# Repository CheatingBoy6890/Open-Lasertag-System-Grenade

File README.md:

<div align="center">

###### Partnering with PCBway.
</div>
<br/>

# Open-Lasertag-System

##  ⚠️Warning⚠️ while this code works it is still wip and could have some bugs
---

https://commons.wikimedia.org/w/index.php?curid=1668938

Warning: This project uses lasers. Be sure to **always** do your own testing by meassuring voltage and current and by looking in datasheets. I am **not** responsible for any injuries you encounter from using this project. Also make sure to wear proper eye-protection.

---

<h2>What is Open-Lasertag-System?</h2>
Open-Lasertag-System is our approach to a build Lasertag that can be played anywhere without the need of setting up repeaters or servers, whilst beeing pretty easy to build and extend to fit your needs. It works decentral using a WIFI mesh,so the range and fun extends the more players you have!

Currently the project consists of five parts:

1.  The Taggers are fully functional with features such as different firemodes and score synchronization
2.  The vests are functional and connect wirelessly with the corresponding tagger
3.  Targets : For those who don't want to shoot at each other can just shoot at these. The plan also ist to intergrate the further into the system for modes like capture the Flag
4.  Logger: Counts wich target have been hit by whom
5.  There's a Laser grenade WIP

---

<h2>What is this repository?</h2>

This is the repository for the grenades of the system. here you'll find all the neccessary files on how to build a grenade your self.

**The instructions on building can be found in the <a href="https://github.com/CheatingBoy6890/Open-Lasertag-System-Grenade/tree/main/Hardware">Hardware folder</a>**

**What you'll need:**

- A 3D-printer capable of printing 20cmx20cm
- Soldering iron
- An ESP 8266 wemos d1 mini
- A piece of LED strip 8 LEDs ws2812b
- At least slightly transparent filament
-  perf matrix board or PCB (comming soon)
- Cable
- Pin headers
- Crimp equipment and or breadboard cables
- Tsop 4838
- 1 IR LED
- 10kΩ resistor
- bc 637 transistor
- 1x Button
- Switch
- Resistor 25Ω
- Battery holder 3 AA batteries
- 4x 6mmx30mm metal rod or pipe

- Time

  ## Who are we?

  We are two German students. Since we are twins, we build and programm a lot of projects together. We create all of our projects in our free time. Feel free to mail any questions to cyberfox3801@proton.me .
  We want to motivate people to discover what is possible using 3D printing and microcontrollers. \
  The most productive worker of our small group is our cat Susi. 

Congratulations you made it to the end of this readme. If you want this to be longer consider buying us a coffe (https://www.paypal.com/donate/?hosted_button_id=2RZBTA5GMNH6S) so we can make all files longer and better
and don't forget to cuddle your cat!

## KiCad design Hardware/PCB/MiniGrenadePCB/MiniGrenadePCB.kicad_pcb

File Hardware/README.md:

<div align="center">

###### Partnering with PCBway.
</div>
<br/>

# Hardware
## General Information 

Warning: This project uses lasers. Be sure to **always** do your own testing by meassuring voltage and current and by looking in datasheets. I am **not** responsible for any injuries you encounter from using this project. Also make sure to wear proper eye-protection.

## Where to get the components
The components are mostly standard components. We recommend buying them in a local store if possible to support the remaining stores.

We recommend ordering the PCBs at PCBWay, because they offer fast delivery and good quality at a low cost.
If you don't have a 3D printer you can also order the parts at PCBWay.

-----

**The Grenade runs using 3 1,2V NiMh batteries! Don't use voltages greater than 5V in order to power it.**

----

  **We recommend not to use a laser diode for the grenade, since it can be dangerous. Use a normal IR LED instead.** 

## The code

To flash the program to your ESP8266 you need to have <a href="https://code.visualstudio.com/">Visual Studio Code</a> and the platformio extension installed. If you haven't you can follow this tutorial:
<a>https://randomnerdtutorials.com/vs-code-platformio-ide-esp32-esp8266-arduino/</a> To flash an ESP8266 from Windows you might need additional drivers, you'll find a tutorial on this here https://randomnerdtutorials.com/install-esp32-esp8266-usb-drivers-cp210x-windows/

## Building the Grenade

#### Perf matrix board
If you're using a perf matrix board, make sure to cut out a 6x6 cm square.

#### PCB
We created the pcb layout with <a href="https://www.kicad.org/">KiCad</a>. You can easily order really nice high-quality PCBs from our partner [PCBWay](www.pcbway.com) by using the PCBWay plugin in KiCAD following this [turorial](https://www.pcbway.com/blog/News/PCBWay_Plug_In_for_KiCad_3ea6219c.html), exporting the gerber files manually like explained [here](https://www.pcbway.com/blog/help_center/How_to_Generate_Gerber_and_Drill_Files_in_KiCad_7_0_ab0d12bb.html) or use the gerber files in the repository (possibly outdated or not-yet available).

----

1. Make sure you have got all the required parts
2. Solder pins to your ESP d1 mini   - Make sure that the ESP8266 board is facing the top. (check and cross from pixabay Bild von <a href="https://pixabay.com/de/users/janjf93-3084263/?utm_source=link-attribution&utm_medium=referral&utm_campaign=image&utm_content=2061132">Jan</a> auf <a href="https://pixabay.com/de//?utm_source=link-attribution&utm_medium=referral&utm_campaign=image&utm_content=2061132">Pixabay</a> Bild von <a href="https://pixabay.com/de/users/openclipart-vectors-30363/?utm_source=link-attribution&utm_medium=referral&utm_campaign=image&utm_content=1292787">OpenClipart-Vectors</a> auf <a href="https://pixabay.com/de//?utm_source=link-attribution&utm_medium=referral&utm_campaign=image&utm_content=1292787">Pixabay</a>
3. Flash the ESP
5. Solder the components to your perf board ore PBC

6. Solder cables to your button
7. Drill a small hole in the grenade shell and glue in the button
8. Solder a switch in the red cable of the battery clip
9. Crimp sockets on your battery clip 
12. Crimp sockets to the cables of the LED strip
13. Crimp sockets to the cables of the button
14. Connect LED strip, button and power
15. Glue the PCB or matrix board in the shell

17. Cut 4 pieces of 6mm x 30mm metal rod or tube
18. Heat up the pieces with a lighter and press them half way into the holes in one half of the shell until

20. Close the shell
21. Screw on the battery cover
22. Cuddle your cat

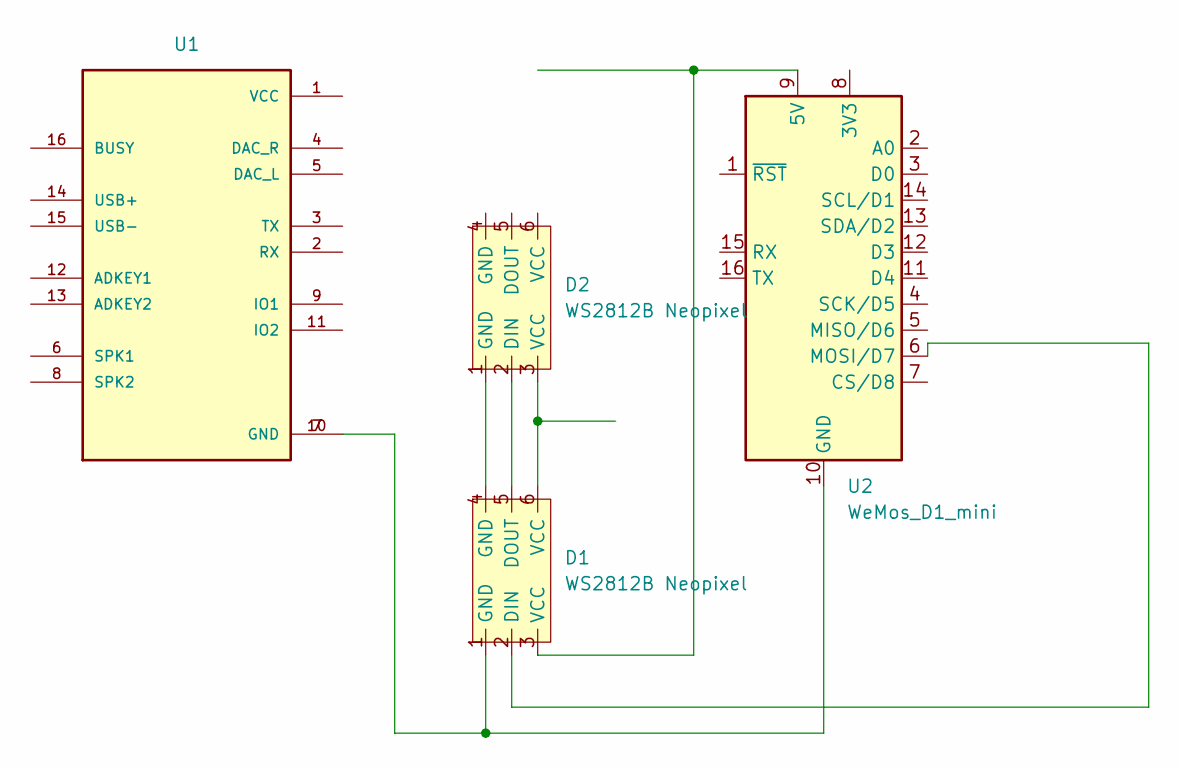
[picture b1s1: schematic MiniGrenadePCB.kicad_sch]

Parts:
D1, D2: WS2812B Neopixel; NeoPixel_strip
U1: DF-Player_mini
U2: WeMos_D1_mini; WEMOS_D1_mini_light

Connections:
unnamed: D1.2 (DIN), U2.6 (MOSI/D7)
unnamed: D1.5 (DOUT), D2.2 (DIN)
unnamed: D1.4 (GND), D2.1 (GND)
unnamed: D1.6 (VCC), D2.3 (VCC)
unnamed: D1.3 (VCC), U2.9 (5V)
unnamed: D1.1 (GND), U1.7 (GND), U1.10 (GND), U2.10 (GND)

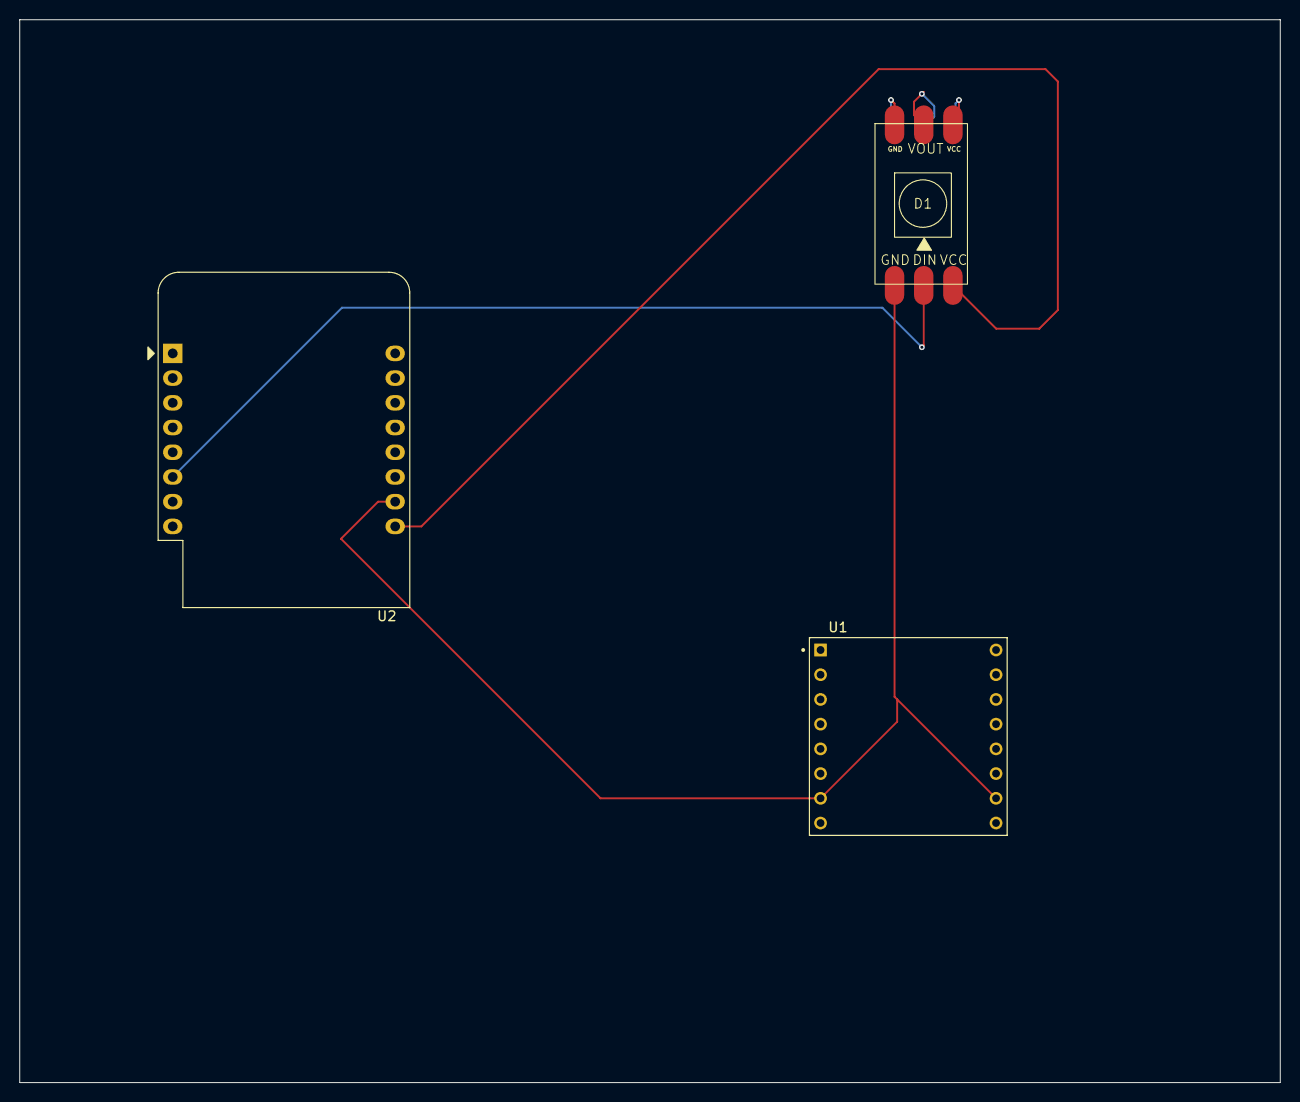
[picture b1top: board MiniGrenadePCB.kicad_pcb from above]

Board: 2 copper layers, 129.5 x 109.2 mm, 4 parts (1 on the bottom side), 6 nets.

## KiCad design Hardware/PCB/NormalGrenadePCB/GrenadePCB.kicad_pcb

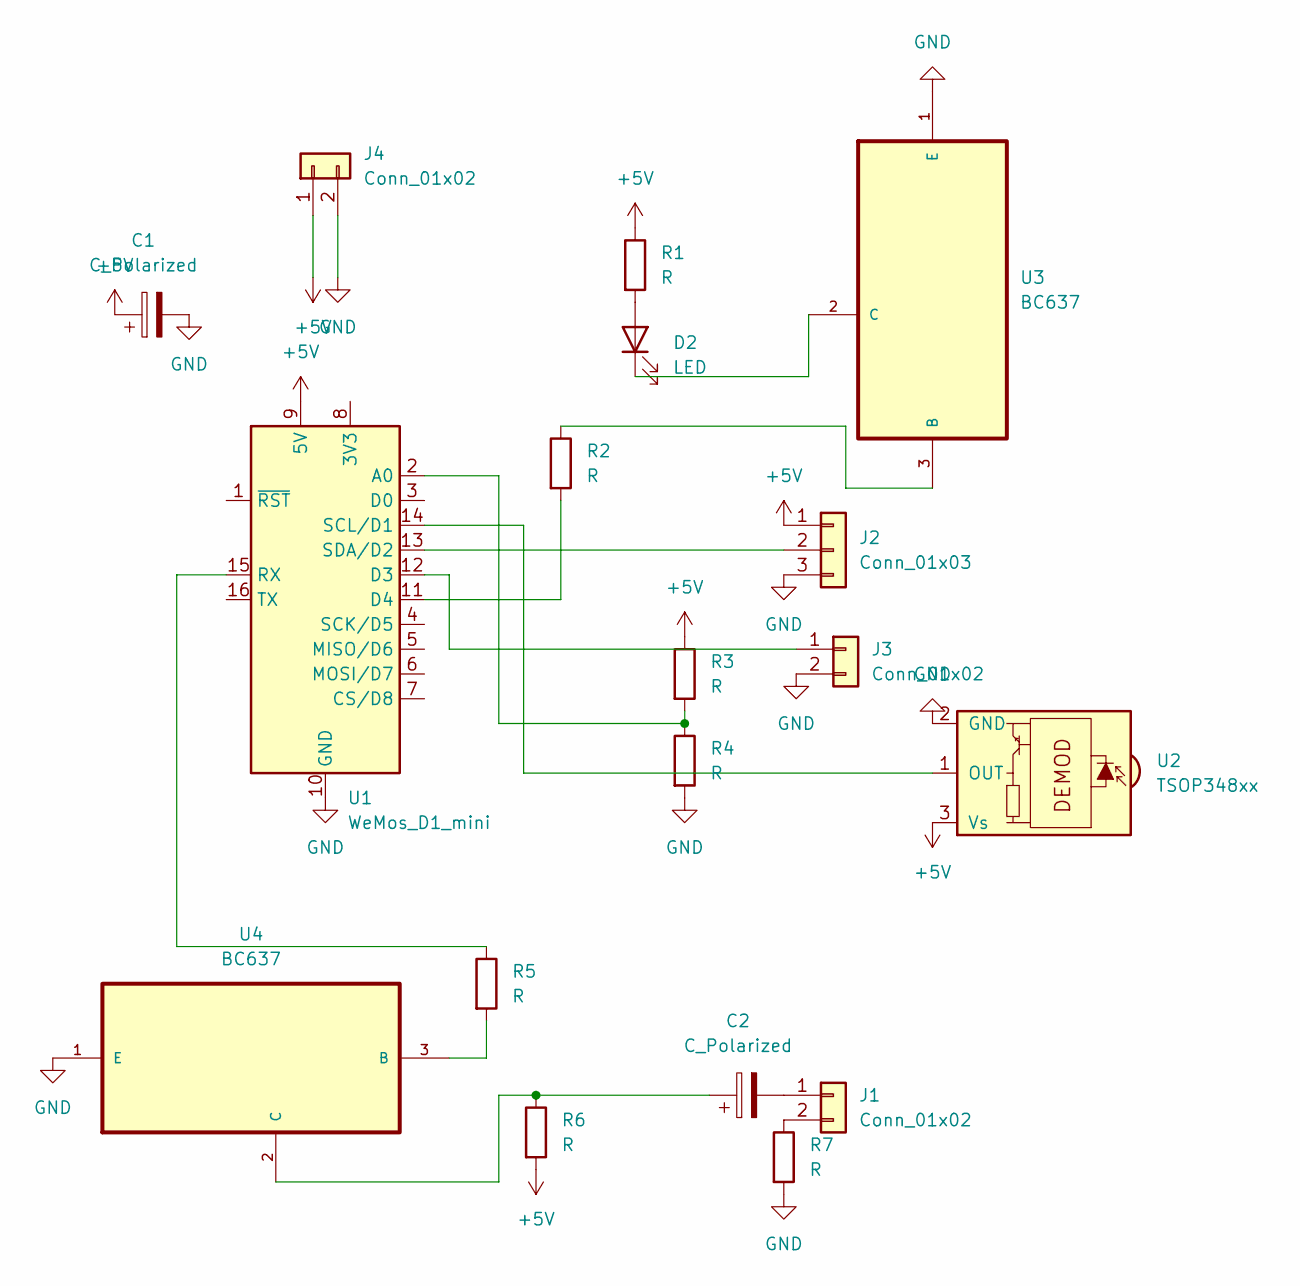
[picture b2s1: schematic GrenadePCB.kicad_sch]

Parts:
C1, C2: C_Polarized; CP_Radial_D7.5mm_P2.50mm
D2: LED; LED_D5.0mm_IRGrey
J1, J3, J4: Conn_01x02; PinHeader_1x02_P2.54mm_Vertical
J2: Conn_01x03; PinHeader_1x03_P2.54mm_Vertical
R1, R2, R3, R4, R5, R6, R7: R; R_Axial_DIN0204_L3.6mm_D1.6mm_P7.62mm_Horizontal
U1: WeMos_D1_mini; WEMOS_D1_mini_light
U2: TSOP348xx; Vishay_MOLD-3Pin
U3, U4: BC637; TO254P508X787-3; MPN BC637

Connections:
+5V: C1.1, J2.1, J4.1, R1.1, R3.1, R6.2, U1.9 (5V), U2.3 (Vs)
GND: C1.2, J2.3, J3.2, J4.2, R4.2, R7.2, U1.10 (GND), U2.2 (GND), U3.1 (E), U4.1 (E)
unnamed: D2.2 (A), R1.2
unnamed: D2.1 (K), U3.2 (C)
unnamed: C2.2, J1.1
unnamed: J1.2, R7.1
unnamed: J2.2, U1.13 (SDA/D2)
unnamed: J3.1, U1.12 (D3)
unnamed: R3.2, R4.1, U1.2 (A0)
unnamed: R2.2, U1.11 (D4)
unnamed: R5.1, U1.15 (RX)
unnamed: U1.14 (SCL/D1), U2.1 (OUT)
unnamed: R2.1, U3.3 (B)
unnamed: R5.2, U4.3 (B)
unnamed: C2.1, R6.1, U4.2 (C)

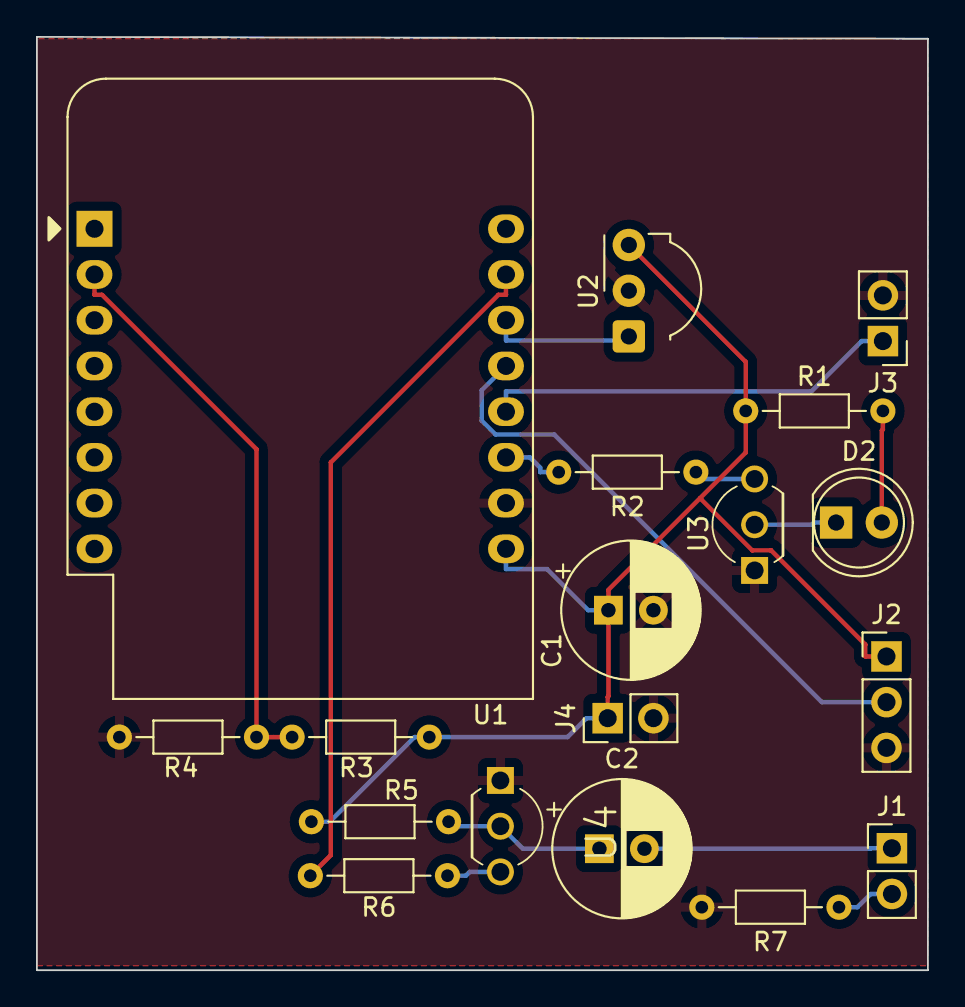
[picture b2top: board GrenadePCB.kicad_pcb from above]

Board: 2 copper layers, 49.5 x 51.9 mm, 18 parts (0 on the bottom side), 15 nets.

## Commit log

2024-08-14 Added the first version of the programm
2024-08-14 Added the 3D files
2024-08-14 Changed the pins
2024-08-16 Update README.md
    Added a line to explain that the Readme is just a copy.
2024-08-21 Added the batter cover stl
2024-08-22 Added image
2024-08-22 Added pictures
2024-09-03 Added the PCBWay Logo
2024-09-03 Added the PCB file
2024-09-14 added sound and fixed PCB
2024-09-22 Fixed sound pin.
2024-10-19 Started adding Mini PCB, with custom footprints in the libraries folders, make sure to add them to KiCAD!
2024-10-19 Corrected PCB Oopsie+ began small grenade PCB
2025-01-11 Started working on the bayonet for the mini grenade
2025-01-11 Added a bayonet from thingiverse (https://www.thingiverse.com/thing:6536797) to the MiniGrenade
